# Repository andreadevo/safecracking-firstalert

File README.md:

# safecracking-firstalert
Building and designing a robot to open a safe with an unknown combination.

Link to photo and video documenation: http://bit.ly/first-alert-documentation

Try times:
100 possible numbers for 3 disks:
100x100x100 = 1,000,000 combinations
Each number can be +/- 1
Not likely or possible to duplicate numbers between disks
33x32x32 = 34,848
13 seconds per test means 5.25 days (without set testing)

We know the disks were only moved around and the first and last disk cannot move.
This means that the first number of the combination has to be 97 and the last must be 0.
1x33x32 = 1,056 combinations
13 seconds per test means 3.81 hours (without set testing)

After looking at the disks inside the safe we saw that they were split into 17 equal, numbered sections where interference points were placed.
The disk closest to the door had one interference point at 9 facing inward towards the safe.
The second two disks were identical and had interference points at 7 on one side and 3 on the other.
Then the disk farthest from the door had an interference point at 10 facing outward towards the door.
We know that the two middle disks are identical and only have two orientations.
We also know that the first and last disks cannot move or be changed.
So we have four possible orientations of the disks and their interference points.
(9)(7/3)(7/3)(10),
(9)(7/3)(3/7)(10),
(9)(3/7)(7/3)(10),
(9)(3/7)(3/7)(10).

This means there are only four possible combinations, one of which is the old one, so in reality, three possible combinations.
(97,32,44,0),
(97,32,??,0),
(97,??,44,0),
(97,??,??,0).

We can guess that most likely both middle disks were flipped to create more mystery
If we find which orientation the old disks were we can model the new orientation and find a range where the missing numbers could be so that we can make our blunt force test WAY faster than 4 hours. Ideally we should find a range of 10 or 15 which would be 3 to 5 set tests.
1x3x3 = 2 minutes
1x5x5 = 5.5 minutes

Even if we settled for finding a range of 48 values (figuring out right/left numbers of dial or top/bottom numbers of dial) it would be 16 tests.
1x16x16 = 55 minutes

Even though we ended up testing only 4 possible combinations, the blunt force test time for the right one (97, 7, 67) would be
1x2x50 = 25 minutes (testing up until getting the correct second number) + 1x1x34 = 8.5 minutes (last test with correct second number until reaching the correct 3rd number).
Being a total of 33.5 minutes to find this particular combination with our tests checking every other number to make up for any slop in the system.

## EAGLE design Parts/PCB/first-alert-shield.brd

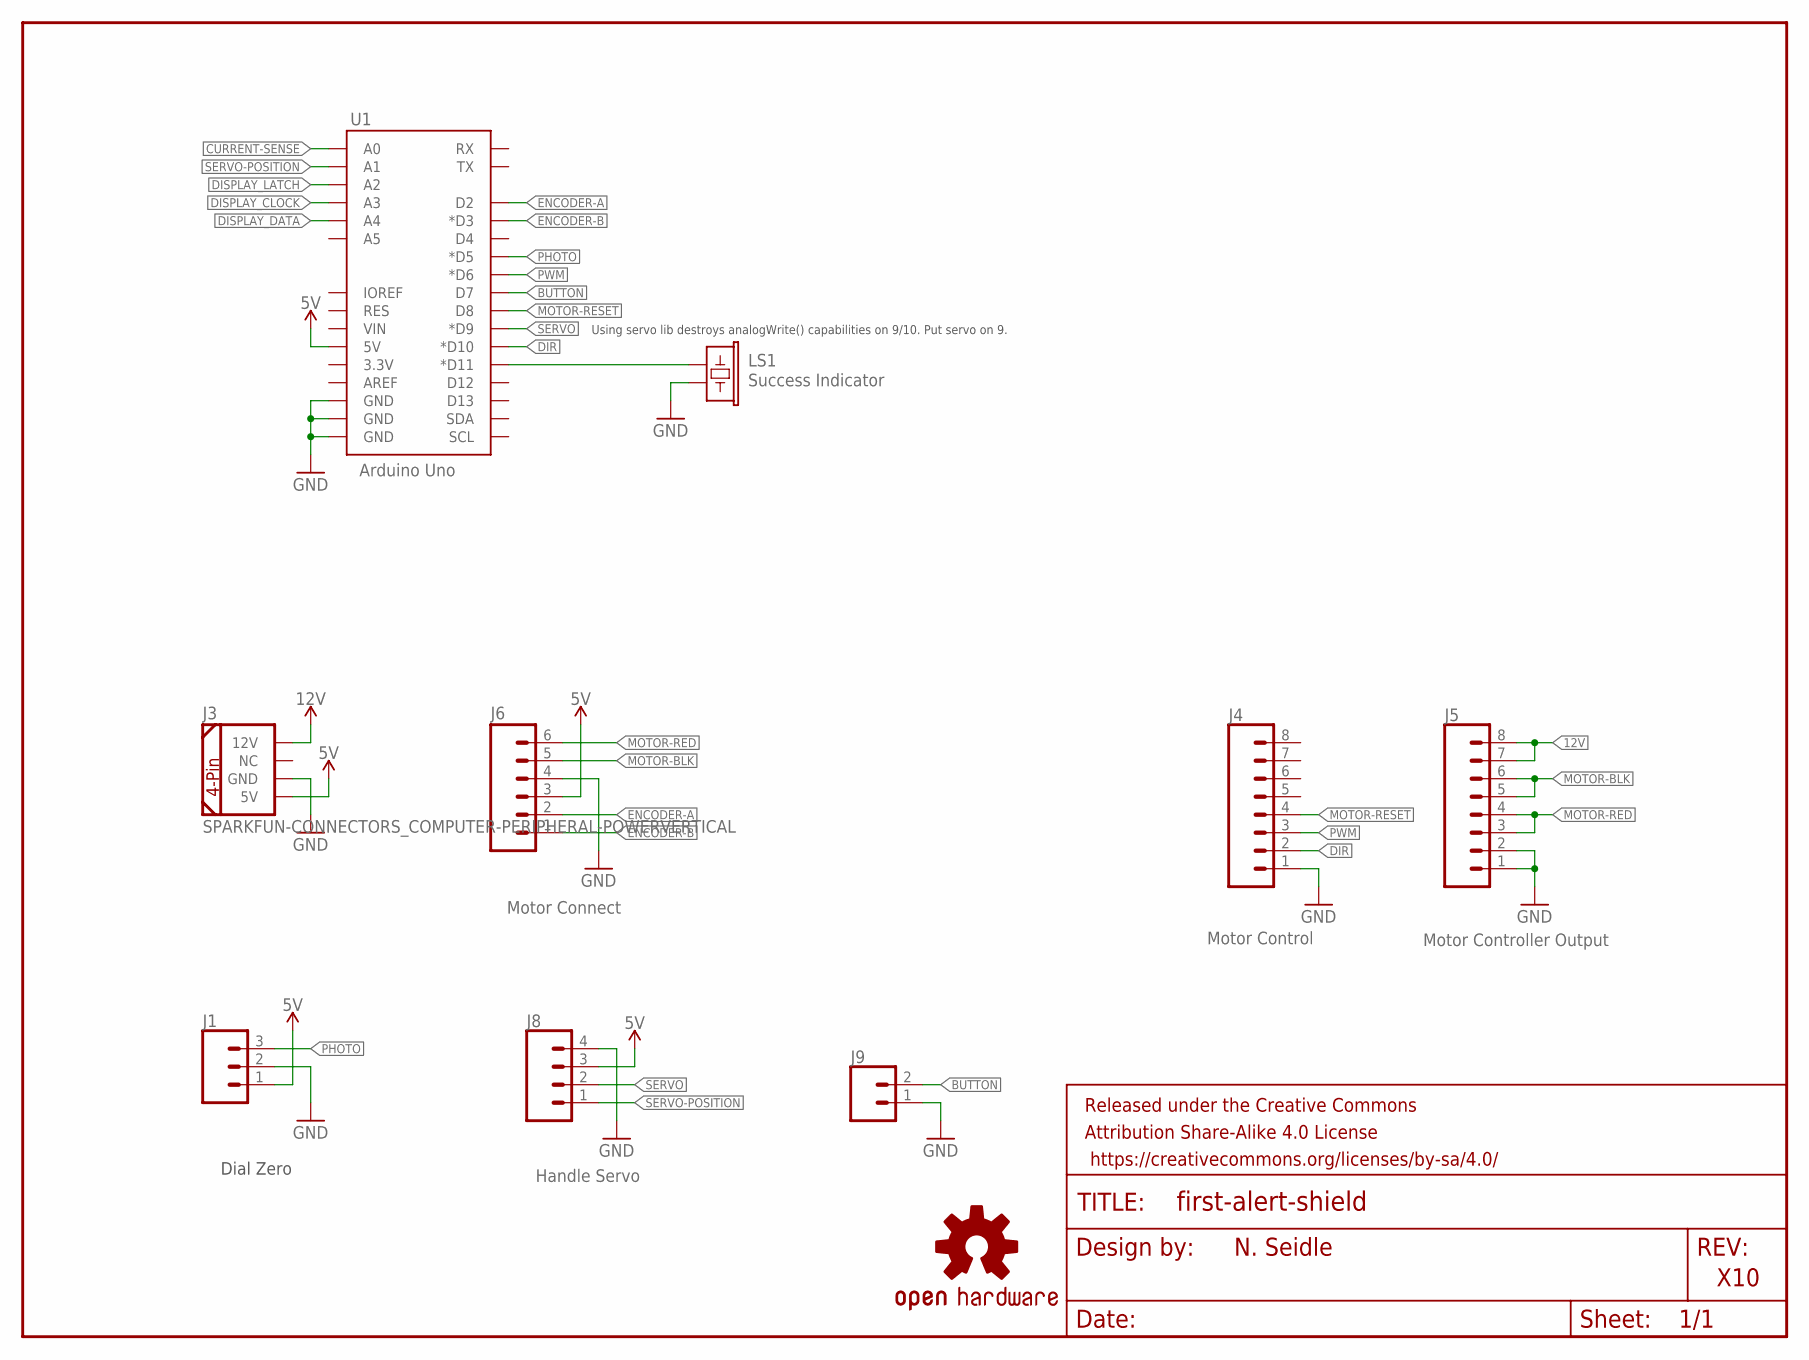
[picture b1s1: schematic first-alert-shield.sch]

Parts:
FRAME1: FRAME-LETTER; CREATIVE_COMMONS
J1: CONN_03JST-PTH-VERT; JST-3-PTH-VERT
J3: SPARKFUN-CONNECTORS_COMPUTER-PERIPHERAL-POWERVERT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; SPARKFUN-CONNECTORS_COMPUTER-PERIPHERAL-POWER
J4: Motor Control; 1X08
J5: Motor Controller Output; 1X08
J6: Motor Connect; 1X06@1
J8: Handle Servo; 1X04
J9: CONN_02JST-PTH-VERT; JST-2-PTH-VERT
LOGO2: OSHW-LOGOS; OSHW-LOGO-S
LS1: Success Indicator; BUZZER-12MM
U1: Arduino Uno; UNO_R3_SHIELD_NOLABELS

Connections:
5V: J1.1, J3.5V, J6.3, J8.3, U1.5V
12V: J3.12V, J5.7, J5.8
BUTTON: J9.2, U1.D7
BUZZ: LS1.+ (1), U1.D11 (*D11)
CURRENT-SENSE: U1.A0
DIR: J4.2, U1.D10 (*D10)
DISPLAY_CLOCK: U1.A3
DISPLAY_DATA: U1.A4
DISPLAY_LATCH: U1.A2
ENCODER-A: J6.2, U1.D2
ENCODER-B: J6.1, U1.D3 (*D3)
GND: J1.2, J3.GND, J4.1, J5.1, J5.2, J6.4, J8.4, J9.1, LS1.- (2), U1.GND@0 (GND), U1.GND@1 (GND), U1.GND@2 (GND)
MOTOR-BLK: J5.5, J5.6, J6.5
MOTOR-RED: J5.3, J5.4, J6.6
MOTOR-RESET: J4.4, U1.D8
PHOTO: J1.3, U1.D5 (*D5)
PWM: J4.3, U1.D6 (*D6)
SERVO: J8.2, U1.D9 (*D9)
SERVO-POSITION: J8.1, U1.A1

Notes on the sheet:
N. Seidle
X10
Using servo lib destroys analogWrite() capabilities on 9/10. Put servo on 9.
Dial Zero

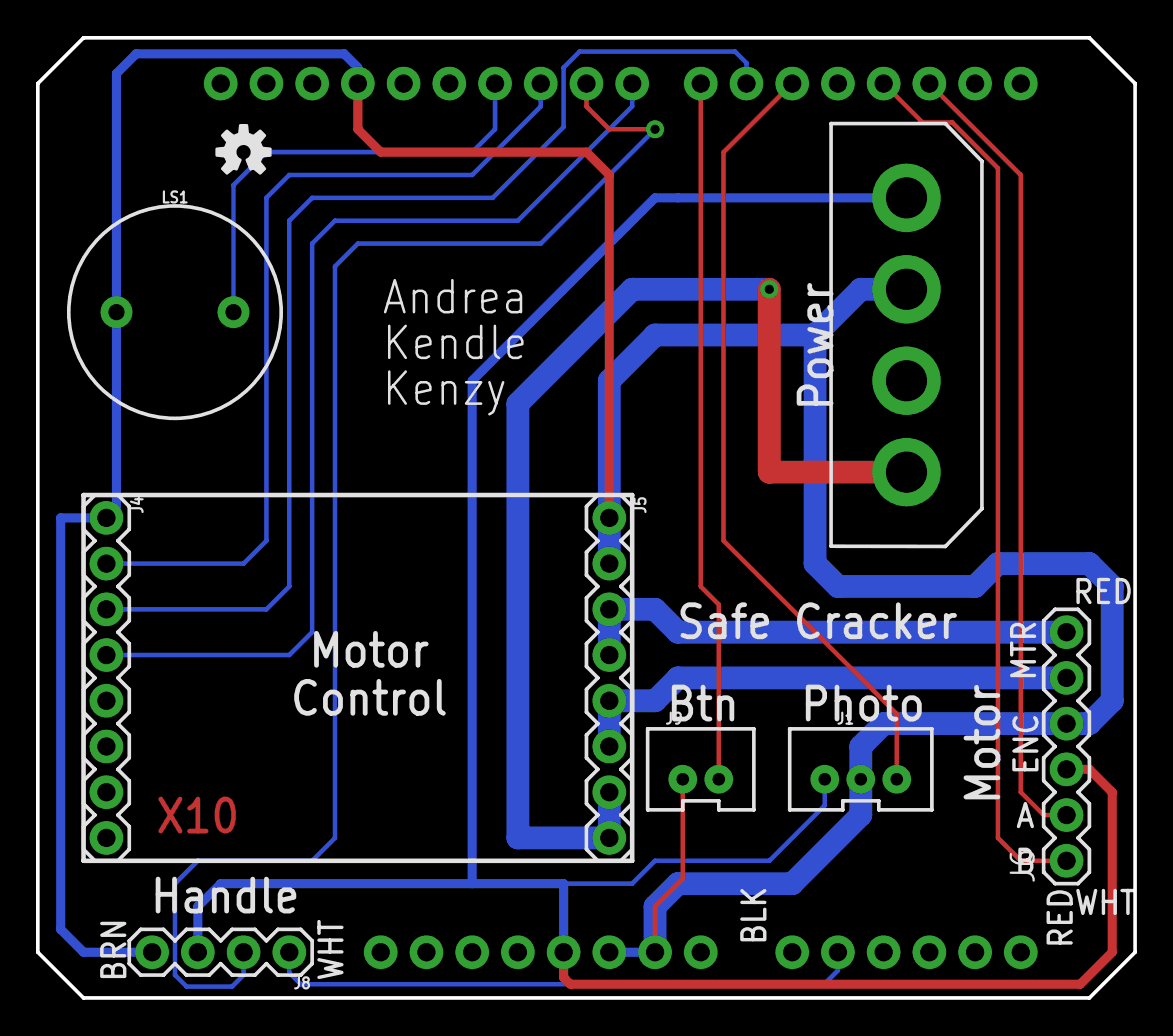
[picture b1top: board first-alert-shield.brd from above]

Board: 2 copper layers, 61.0 x 53.3 mm, 11 parts (0 on the bottom side), 15 nets.

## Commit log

2018-09-26 handle puller model prototype with lever
2018-09-26 basic handle puller prototype
2018-09-26 3D Print FIles Handle and Coupler
2018-10-07 cleaning out repo to only have final products
2018-10-07 cleaning up github repo into final group documentation
2018-10-08 Update MotorDriver/MotorDriver.ino
    Motor Driver code that changes motor direction and stops the motor with a photogate
2018-10-08 Update MotorDriver/MotorDriver.ino
    Changed encoder readings and print statements
2018-10-08 example code of command prompt interactivity
2018-10-10 Changed if statements for dial input
2018-10-10 sketch to check encoder reset
2018-10-10 sketch to check resetting encoder
2018-10-10 Encoder ticks working in both directions.
2018-10-10 Home changed and encoder ticks converted to dial positions.
2018-10-15 Cleaned up prints and created an error message for nonexistant dial positions.
2018-10-17 Changed menu and broke functions into tabs.
2018-10-20 More math and better menus
2018-10-24 findHome now maps to the dial properly
2018-10-26 Added an openSafe function, cleaned up menu, added a gotToZero
2018-10-29 Edited openSafe() to be smaller
2018-10-29 first attempt altering PCD board, removed extra components, altered power connector, reconnected traces from power connector
2018-10-31 Motor rotates correctly to put in the combination,
2018-11-28 Dial positions are mapped backwards
2018-12-01 it works!
2018-12-03 opened safe, added set testing
2018-12-03 Encoder is fixed and we have a working sanity sketch
2018-12-05 Encoder "mostly" calibrated
2018-12-05 We're calibrated!
2018-12-05 Slow down functions implemented, still kind of fine tuning calibration
2018-12-08 Everything is working and we can blunt force the safe open with a working win state
2018-12-08 3D models for safe
2018-12-08 Updated coupler
2018-12-08 Organized
2018-12-10 Changed a few numbers added a few prints
2018-12-12 Changed testing range to be full range
2018-12-13 Update README.md
    Added a link to photo and video documentation

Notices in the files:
parts and their libraries:
SparkFun-Aesthetics: Licensing: CC v3.0 Share-Alike You are welcome to use this library for commercial purposes.
SparkFun-Aesthetics: Released under the Creative Commons Attribution Share-Alike 4.0 License
SparkFun-Aesthetics: https://creativecommons.org/licenses/by-sa/4.0
